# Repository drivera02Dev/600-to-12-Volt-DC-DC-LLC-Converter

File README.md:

# 600V-to-12V-DC-DC-Converter-Senior-Design-Project
## Team
- Caleb Rezmer 
- Drew Bixler 
- Hunter Kanne 
- Diego Rivera 
- Andrew Chandler 
- Wesley Mao

## Overview
This project was proposed by Caleb Rezmer for the FSAE club at Iowa State. This converter will go inside the electric formula car and it will use the 600 Volt battery from the car and step it down to 12 Volts at 30 Amps. It is stepped down to 12 Volts for the internals of the car such as lights, digital displays, fans, and anything else the team would want to add to the car that requires low voltage.

## Role
My role in the project was to make sure the power supply had the proper components it needs to function properly. I had to build and edit the schematic from the reference design we had. I had to verify that at the proper test points it was able to take that high voltage and keep the voltage at a steady 12 volts.

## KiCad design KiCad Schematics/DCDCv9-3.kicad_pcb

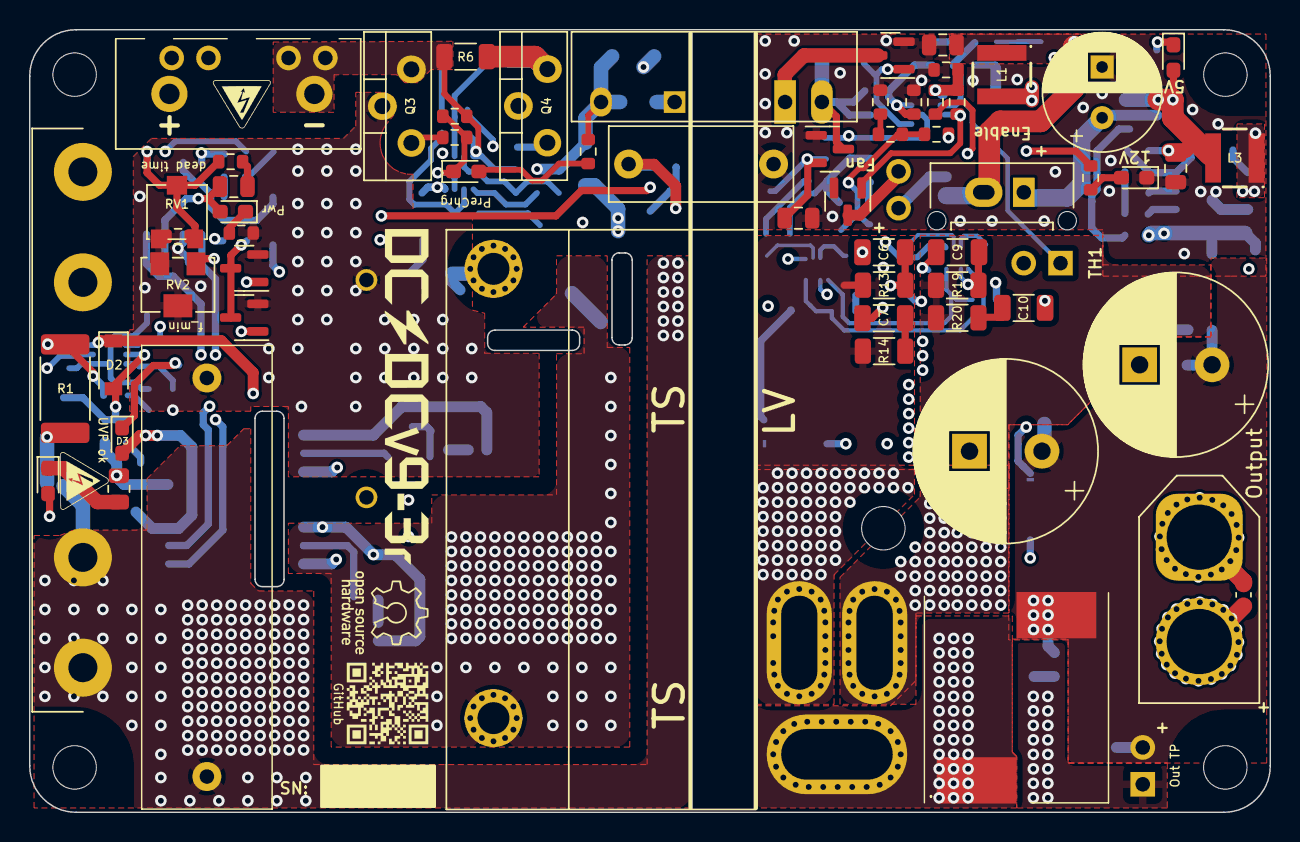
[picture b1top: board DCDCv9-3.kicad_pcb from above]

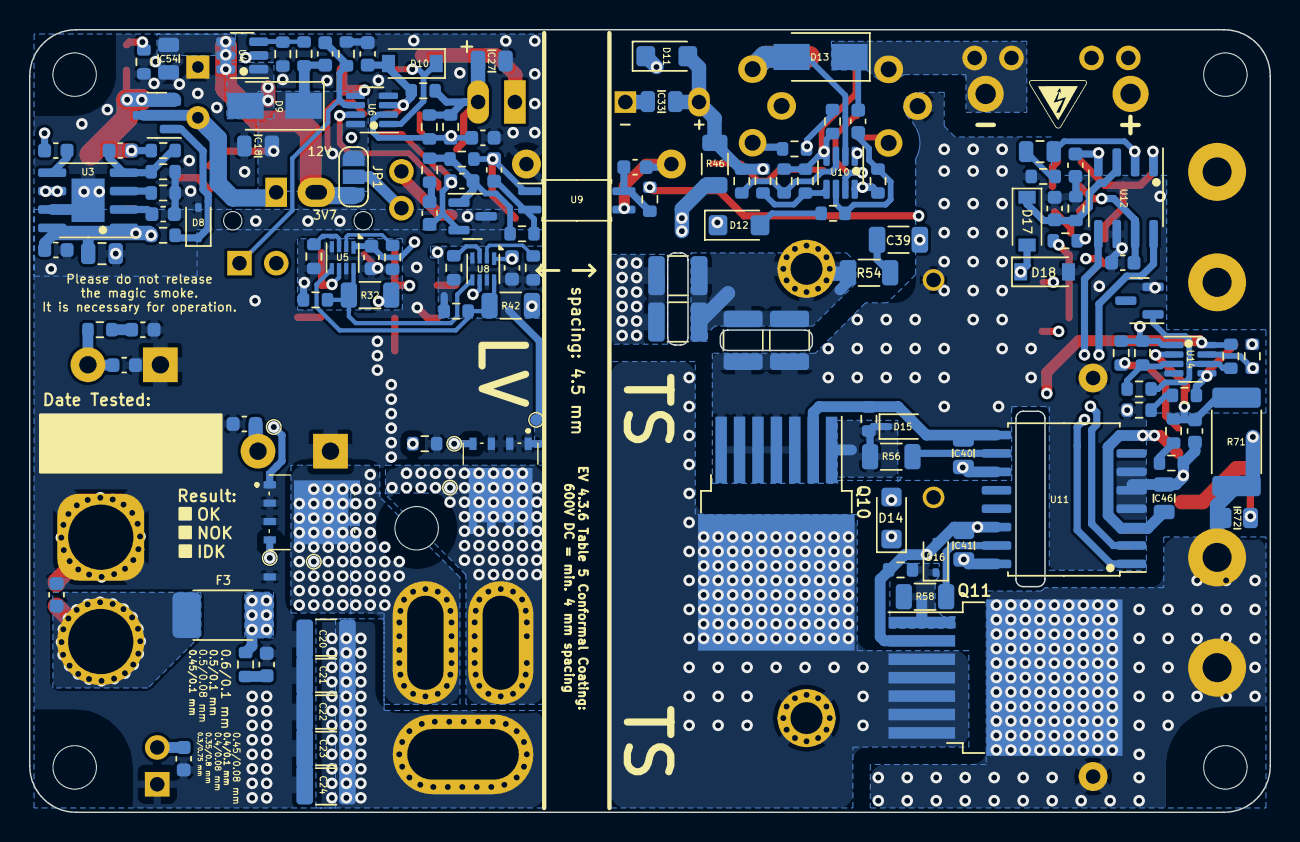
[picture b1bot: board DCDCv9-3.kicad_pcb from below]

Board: 4 copper layers, 85.6 x 54.0 mm, 206 parts (139 on the bottom side), 102 nets.

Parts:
C1: 2uF; MKP1848520704K2
C2, C15, C40, C41: 2.2uF; C_0805_2012Metric
C3: 22nF; R76UI22205050J
C4: 3.3nF; C_Disc_D12.5mm_W5.0mm_P10.00mm
C5, C33, C46: 10uF; C_0805_2012Metric
C6, C9: 1 nF; C_1206_3216Metric
C7, C10, C39: 470pF; C_1206_3216Metric
C8, C12, C18, C27, C42, C54: 22uF; C_0805_2012Metric
C11, C13: 2200uF; CP_Radial_D12.5mm_P5.00mm_symbol_inside
C14, C28: 100nF; C_0603_1608Metric
C16, C49, C50, C51, C52, C53, C55, C56, C57: 1nF; C_0603_1608Metric
C17, C19, C25, C31, C45: 1uF; C_0603_1608Metric
C20, C21, C22, C23, C24: 10uF; C_1210_3225Metric
C26, C44, C47: 22nF; C_0603_1608Metric
C29: 47pF; C_0603_1608Metric
C30, C32, C48: 10nF; C_0603_1608Metric
C34, C35, C36, C37: 5.6nF; C_1210_3225Metric
C38: 120pF; C_0603_1608Metric
C43: 470nF; C_0603_1608Metric
C_start1: 3.8V 25F Supercap; CP_Radial_D8.0mm_P3.50mm
D1: HV_Orange; LED_0603_1608Metric_Pad1.05x0.95mm_HandSolder
D2, D10, D17, D18: 1N4448; D_SOD-123
D3, D4, D5, D6, D7: Green; LED_0603_1608Metric_Pad1.05x0.95mm_HandSolder
D8, D15, D16: CDSOD323-T12; D_SOD-323
D9, D13: SS1H10; D_SMA
D11, D12, D14: VS-E7FX0212-M3/I; D_SMF
F1: 1.6A; Fuseholder0,25Zoll_32mm_littlefuse_102_122
F3: 20A; Bel_SMCF_Fuse_2410_6125Metric
HV_Logo_1, HV_Logo_1#2, HV_Logo_1#3: HV_Logo_1; HV_Logo_small
J1: Screw_Terminal_01x03; TerminalBlock_TE-282817-2_1x03_P5.00mm_90 Degrees updated v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
J2, J4, J6, J7, J8: Conn_01x02_Male; PinHeader_1x02_P2.54mm_Vertical
J3: Conn_01x02; Molex_Micro-Fit_3.0_43650-0215_1x02_P3.00mm_Vertical_combin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
J5: XT60 Male; AMASS_XT60-F_1x02_P7.20mm_Vertical
JP1: Fan Voltage Select; SolderJumper-3_P1.3mm_Open_RoundedPad1.0x1.5mm_NumberLabels
L1: 4.7uH; ASPI-4030S
L2: 1uH; 7443091100_v9.2
L3: 10uH; ASPI-4030S
NT1, NT2: NetTie_2; dummy_net_line_0.5mm
Q1, Q2, Q5, Q6, Q7: PMV20ENR; SOT-23
Q3: SIHP24N80AE-GE3; TO-220-3_Vertical_HV1.2mm
Q4: IXYP8N90C3; TO-220-3_Vertical_HV1.2mm
Q8, Q9: BSC027N06LS5ATMA1
Q10, Q11: IMBG65R050M2HXTMA1; TO-263-7_TabPin8
QR_Coode_1: QR_Coode; GitHub_QR_Code
R1, R71: 100M; R_2512_6332Metric_Pad1.40x3.35mm_HandSolder
R2, R72: 330k; R_0805_2012Metric
R3: 3.0k; R_0603_1608Metric
R4, R39, R41, R59, R61: 1k; R_0603_1608Metric
R5, R7, R9, R11, R15, R16, R21, R23, R30, R33, R40, R43, R51, R52, R55, R57, R63: 10k; R_0603_1608Metric
R6, R14, R20: 47; R_1206_3216Metric
R8, R10, R22, R29, R38, R48, R49: 2.2k; R_0603_1608Metric
R12: 910; R_0603_1608Metric
R13, R19: 100; R_1206_3216Metric
R17, R24: 27k; R_0603_1608Metric
R18, R27, R50: 470k; R_0603_1608Metric
R25: 240k; R_0603_1608Metric
R26, R45, R47, R53, R67, R70: 100k; R_0603_1608Metric
R28, R34, R66: 33k; R_0603_1608Metric
R31, R36: 4.7k; R_0603_1608Metric
R32, R42: 4.7; R_1206_3216Metric
R35: 330k; R_0603_1608Metric
R37: 47k; R_0603_1608Metric
R44: 510; R_0603_1608Metric
R46: 20; R_1206_3216Metric
R54: 10M; R_1206_3216Metric
R56, R58: 10; R_1206_3216Metric
R60: 82k; R_0603_1608Metric
R62, R69: 100M; R_0603_1608Metric
R64: 820k; R_0603_1608Metric
R65: 510k; R_0603_1608Metric
R68: 1.6M; R_0603_1608Metric
R73, R74: 10; R_0603_1608Metric
RV1: 20k; Potentiometer_Bourns_PVG3G
RV2: 10k; Potentiometer_Bourns_3214W_Vertical
T1: DIY Transformer ETD 39; Transformer_ETD39_uprightV3.6 (PSS 24V)
TH2: 1k PTC; R_0603_1608Metric
TP1, TP2, TP3, TP4, TP5, TP6: TestPoint; TestPoint_Pad_D0.8mm_DC-DC
TP8: GaN GND2; TestPoint_Pad_D0.8mm_DC-DC
U1: TBA 1-1212HI; Converter_DCDC_TRACO_TBA 1-1212HI-3kV-iso
U2: RT9058-90GVL; SOT-23
U3: MP4541_SOP8-EP; SOIC-8-1EP_3.9x4.9mm_P1.27mm_EP2.29x3mm XL7005
U4: TLV61048DBVR; SOT-23-6
U5, U8: NCP4305DMTTWG; WDFN-8_2x2mm_P0.5mm
U6, U10, U14: LM2904BIDDFR; SOT-23-8_DC-DC_v9
U7: TL431; SOT-23
U9: ACPL-217-50AE; SOIC-4_4.55x2.6mm_P1.27mm
U11: UCC21520DW; SOIC-16W_7.5x10.3mm_P1.27mm
U12: UCC25600; SOIC-8_3.9x4.9mm_P1.27mm
U13: ZXRE330ASA-7; SOT-23

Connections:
24V_TP: C11.1, C13.1, C50.2, C51.2, C52.2, F3.1, J4.1, L2.2, R17.1, R73.1, R74.1
+3V7: C8.1, C54.1, J3.2, JP1.3 (B), L1.1, U4.4 (~SHDN), U4.5 (IN), U4.6 (nc)
+9V: C5.1, C30.2, R39.1, U2.2 (VO), U9.1
+12V_HS: C41.2, D14.1 (K), U11.16 (VDDA)
+12V_IN: C2.2, C40.2, C45.2, C46.1, D2.1 (K), D3.2 (A), D4.2 (A), D11.1 (K), R70.1, U11.3 (VCCI), U11.8 (VCCI), U11.11 (VDDB), U12.7 (VCC), U14.8 (V+)
+12V_sw: C18.1, C19.2, C25.1, C27.1, C31.1, D9.1 (K), J8.1, JP1.1 (A), R16.1, R21.2, R27.1, R34.1, R35.2, R36.2, U1.1 (+VIN), U2.3 (VI), U5.1 (VCC), U6.8 (V+), U8.1 (VCC)
+24V: C15.2, C53.2, R26.2, U3.1 (EN), U3.8 (VIN)
+HV: C1.2, C34.1, C35.1, F1.2, Q11.8 (D), R1.1, R71.1, R72.1
+HV_in: F1.1, J1.2, J7.1, J7.2
-HV_in: C33.2, C38.1, D13.1 (K), J1.1, J6.1, J6.2, Q3.3 (S), R6.2, R7.2, R48.1, R50.1, R51.2, U1.5 (-VOUT), U10.4 (V-)
-HV_pc: C1.1, C3.2, C4.1, C32.2, C36.2, C37.2, C43.2, C44.1, C45.1, C46.2, C47.2, D12.1 (K), D18.2 (A), Q1.2 (S), Q2.2 (S), Q3.2 (D), Q4.2 (C), Q10.3 (S), Q10.4 (S), Q10.5 (S), Q10.6 (S), Q10.7 (S), R2.2, R3.2, R5.1, R59.2, R60.1, R65.2, R68.2, RV1.3, RV2.2, RV2.3, U9.3, U11.4 (GND), U11.5 (DIS), U11.6 (DT), U12.6 (GND), U13.2, U14.4 (V-)
/HB_out: Q10.8 (D), Q11.3 (S), Q11.4 (S), Q11.5 (S), Q11.6 (S), Q11.7 (S), T1.1 (AA)
/HS: U11.1 (INA), U12.8 (GD1)
/LS: U11.2 (INB), U12.5 (GD2)
/OC: C44.2, D17.1 (K), R60.2, U12.3 (OC)
/OTP_FAN: Q5.1 (G), R18.1, U6.7
/OTP_OFF: D10.1 (K), Q6.1 (G), U6.1
/OVP: Q2.1 (G), R69.1, U14.7
/Opc+: C32.1, R44.2, U9.4
/Synchronous Rectification/3: Q9.5 (D_1), Q9.6 (D_2), Q9.7 (D_3), Q9.8 (D_4), Q9.9 (D_5), R13.2, R14.1, T1.3 (SB), TP5.1
/Synchronous Rectification/5: Q8.5 (D_1), Q8.6 (D_2), Q8.7 (D_3), Q8.8 (D_4), Q8.9 (D_5), R19.2, R20.1, T1.5 (SA), TP3.1
/UVP: Q1.1 (G), R62.1, R63.1, U14.1
GND: C4.2, C5.2, C7.1, C8.2, C10.1, C11.2, C12.1, C13.2, C15.1, C17.1, C18.2, C20.2, C21.2, C22.2, C23.2, C24.2, C27.2, C28.1, C48.1, C49.1, C50.1, C51.1, C52.1, C53.1, C54.2, C55.1, C56.1, C57.1, C_start1.2 (-), D6.1 (K), D8.2 (A2), J4.2, J5.2, NT1.2, NT2.2, Q5.2 (S), Q6.2 (S), Q8.1 (S_1), Q8.2 (S_2), Q8.3 (S_3), Q9.1 (S_1), Q9.2 (S_2), Q9.3 (S_3), R10.2, R11.2, R15.1, R22.1, R23.2, R25.1, R28.2, R31.1, TH2.2, TP8.1, U2.1 (GND), U3.7 (GND), U4.2 (GND), U6.4 (V-), U7.3 (A)
unnamed: C2.1, R4.2
unnamed: C7.2, R14.2
unnamed: C10.2, R20.2
unnamed: C26.2, R37.1
unnamed: C30.1, R41.1, U9.2
unnamed: C39.2, R54.1
unnamed: C42.2, R59.1
unnamed: C56.2, R73.2
unnamed: C57.2, R74.2
unnamed: C_start1.1 (+), J3.1, Q7.3 (D)
unnamed: D1.2 (A), R72.2
unnamed: D1.1 (K), R2.1
unnamed: C47.1, D2.2 (A), R67.2, R71.2, U14.2 (-)
unnamed: D3.1 (K), R63.2
unnamed: D4.1 (K), R5.2
unnamed: D5.2 (A), R9.1
unnamed: D5.1 (K), R7.1, R8.2, U10.7
unnamed: D6.2 (A), R21.1
unnamed: C12.2, C16.2, D7.2 (A), L3.2, Q7.2 (S), R24.1
unnamed: D7.1 (K), R22.2
unnamed: D8.1 (A1), Q7.1 (G), R26.1
unnamed: D9.2 (A), L1.2, U4.1 (SW)
unnamed: C48.2, D10.2 (A), R11.1, R34.2, U6.3 (+)
unnamed: C33.1, D11.2 (A), R9.2, R45.2, R46.2, R47.2, R53.2, U1.7 (+VOUT), U10.8 (V+)
unnamed: D12.2 (A), R52.1
unnamed: D13.2 (A), Q4.3 (E), R6.1, U10.2 (-)
unnamed: D14.2 (A), R46.1
unnamed: D15.1 (A1), Q10.1 (G), R55.1, R56.1
unnamed: C40.1, D15.2 (A2), Q10.2 (DS), R55.2, U11.9 (VSSB)
unnamed: D16.1 (A1), Q11.1 (G), R57.1, R58.1
unnamed: C41.1, D16.2 (A2), Q11.2 (DS), R57.2, U11.14 (VSSA)
unnamed: C39.1, D17.2 (A), D18.1 (K)
unnamed: J2.1, JP1.2 (C)
unnamed: J2.2, Q5.3 (D)
unnamed: C49.2, C55.2, F3.2, J5.1
unnamed: C19.1, J8.2, R31.2, U6.6 (-)
unnamed: Q1.3 (D), Q2.3 (D), R61.1
unnamed: Q3.1 (G), R8.1
unnamed: Q4.1 (G), R49.1
unnamed: Q8.4 (G), R32.1, TP2.1
unnamed: Q9.4 (G), R42.1, TP4.1
unnamed: R10.1, R12.2
unnamed: R49.2, R51.1, U10.1
unnamed: R65.1, R66.2
unnamed: R67.1, R68.1
unnamed: C34.2, C35.2, C36.1, C37.1, R54.2, T1.2 (AB)
unnamed: C20.1, C21.1, C22.1, C23.1, C24.1, L2.1, T1.4 (SC)
unnamed: C14.2, U3.5 (BST)
unnamed: C16.1, R23.1, R24.2, U3.4 (FB)
unnamed: R25.2, U3.3 (FREQU)
unnamed: C14.1, L3.1, U3.6 (SW)
unnamed: C17.2, U3.2 (VCC)
unnamed: R27.2, R28.1, U4.3 (FB)
unnamed: C9.2, R19.1, U5.6 (CS)
unnamed: R30.2, R32.2, U5.8 (DRV), U8.5 (TRIG/DIS)
unnamed: C9.1, C25.2, NT1.1, R29.1, R30.1, R33.1, TP1.1, U5.4 (LLD), U5.7 (GND)
unnamed: R33.2, U5.2 (MIN_TOFF)
unnamed: R29.2, U5.3 (MIN_TON)
unnamed: R40.2, R42.2, U5.5 (TRIG/DIS), U8.8 (DRV)
unnamed: C28.2, R35.1, R36.1, TH2.1, U6.2 (-)
unnamed: R15.2, R16.2, R18.2, U6.5 (+)
unnamed: C29.2, R37.2, R39.2, R41.2, U7.1 (K)
unnamed: C26.1, C29.1, R12.1, R17.2, U7.2 (REF)
unnamed: C6.2, R13.1, U8.6 (CS)
unnamed: C6.1, C31.2, NT2.1, R38.1, R40.1, R43.1, TP6.1, U8.4 (LLD), U8.7 (GND)
unnamed: R43.2, U8.2 (MIN_TOFF)
unnamed: R38.2, U8.3 (MIN_TON)
unnamed: R45.1, R48.2, U10.3 (+)
unnamed: R47.1, R50.2, U10.5 (+)
unnamed: C38.2, R52.2, R53.1, U10.6 (-)
unnamed: R58.2, U11.15 (OUTA)
unnamed: R56.2, U11.10 (OUTB)
unnamed: R3.1, R4.1, RV1.1, RV1.2, U12.1 (DT)
unnamed: C42.1, R44.1, RV2.1, U12.2 (RT)
unnamed: C43.1, R61.2, U12.4 (SS)
unnamed: R62.2, R64.1, U14.3 (+)
unnamed: R1.2, R66.1, R69.2, U14.5 (+)
unnamed: R64.2, R70.2, U13.1, U14.6 (-)
OTP_FET: Q6.3 (D), U1.2 (-VIN)

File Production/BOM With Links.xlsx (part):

Reference | Value | Manufacturer_Part_Number |  |  | DigiKey Link |  |  |  |  |  |  |  |  |  |  |  |  |  | Price | # of Parts | Total (Parts Only)
C1 | 2uF | MKP1848520704K2 |  | Mouser | https://www.mouser.com/ProductDetail/Vishay-Roederstein/MKP1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 |  |  |  |  |  |  |  |  |  |  |  |  |  | 3.92 | 1 | 141.76999999999992
C3 | 22nF | R76UI22205050J |  |  | https://www.digikey.com/en/products/detail/kemet/R76UI222050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 |  |  |  |  |  |  |  |  |  |  |  |  |  | 0.88 | 1
C4 | 3.3nF | VY1332M59Y5UQ63V0 |  |  | https://www.digikey.com/en/products/detail/vishay-beyschlag-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 |  |  |  |  |  |  |  |  |  |  |  |  |  | 0.74 | 1
C29 | 1V | C0603C470J1HACTU |  |  | https://www.digikey.com/en/products/detail/kemet/C0603C470J1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 |  |  |  |  |  |  |  |  |  |  |  |  |  | 0.1 | 1
C39 | 470pF | 885342208005 |  |  | https://www.digikey.com/en/products/detail/w%C3%BCrth-elektr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 |  |  |  |  |  |  |  |  |  |  |  |  |  | 0.21 | 1
C43 | 470nF | UMK107ABJ474KA-T |  |  | https://www.digikey.com/en/products/detail/taiyo-yuden/UMK10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 |  |  |  |  |  |  |  |  |  |  |  |  |  | 0.13 | 1
C11,C13 | 2200uF | UHW1V222MHD |  |  | https://www.digikey.com/en/products/detail/nichicon/UHW1V222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 |  |  |  |  |  |  |  |  |  |  |  |  |  | 2.4300000000000002 | 1
C14,C28 | 100nF | HMJ107BB7104KAHT |  |  | https://www.digikey.com/en/products/detail/taiyo-yuden/HMJ10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 |  |  |  |  |  |  |  |  |  |  |  |  |  | 0.54 | 2
C15,C40,C41 | 2.2uF | CL21B225KBYNNWE |  | Mouser | https://www.mouser.com/ProductDetail/Samsung-Electro-Mechani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 |  |  |  |  |  |  |  |  |  |  |  |  |  | 0.23 | 1
C16,C49,C50,C51,C52,C53,C56,C57 | 1nF | 885342206003 |  |  | https://www.digikey.com/en/products/detail/w%C3%BCrth-elektr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 |  |  |  |  |  |  |  |  |  |  |  |  |  | 0.8 | 8
C17,C19,C25,C31,C45 | 1uF | CL10B105KB9VPJC |  | Substitute | https://www.digikey.com/en/products/detail/samsung-electro-m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 |  |  |  |  |  |  |  |  |  |  |  |  |  | 1.44 | 4
C20,C21,C22,C23,C24 | 47uF | MSAST32MAB5476MPNDT1 | Mouser | Swapped | https://www.mouser.com/ProductDetail/TAIYO-YUDEN/MSAST32MAB5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 |  |  |  |  |  |  |  |  |  |  |  |  |  | 3.92 | 4
C26,C44,C47 | 22nF | C0603C223K1RAC |  |  | https://www.digikey.com/en/products/detail/kemet/C0603C223K1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 |  |  |  |  |  |  |  |  |  |  |  |  |  | 0.30000000000000004 | 3
C30,C32,C48 | 10nF | C0603C103K2RECTU |  |  | https://www.digikey.com/en/products/detail/kemet/C0603C103K2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 |  |  |  |  |  |  |  |  |  |  |  |  |  | 0.44999999999999996 | 3
C34,C35,C36,C37 | 5.6nF | C1210C562JDGACAUTO |  |  | https://www.digikey.com/en/products/detail/kemet/C1210C562JD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 |  |  |  |  |  |  |  |  |  |  |  |  |  | 7.72 | 4
C5,C33,C46 | 10uF | TMK212BBJ106KG-T |  |  | https://www.digikey.com/en/products/detail/taiyo-yuden/TMK21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 |  |  |  |  |  |  |  |  |  |  |  |  |  | 0.48 | 3
C6,C9 | 1 nF | SH31B102K631CT |  | Mouser | https://www.mouser.com/ProductDetail/Walsin/SH31B102K631CT?q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 |  |  |  |  |  |  |  |  |  |  |  |  |  | 0.22 | 2
C8,C12,C18,C27,C42,C54 | 22uF | CL21A226MAYNNNE |  |  | https://www.digikey.com/en/products/detail/samsung-electro-m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 |  |  |  |  |  |  |  |  |  |  |  |  |  | 1.44 | 6
C_start1 | 3.8V 25F Supercap | VMF256M3R8 |  |  | https://www.digikey.com/en/products/detail/cornell-dubilier-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 |  |  |  |  |  |  |  |  |  |  |  |  |  | 5.33 | 1
D1 | HV_Orange | APTD1608LSECK/J4-PF |  |  | https://www.digikey.com/en/products/detail/kingbright/APTD16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 |  |  |  |  |  |  |  |  |  |  |  |  |  | 0.59 | 1
D11,D12,D14 | VS-E7FX0212-M3/I | VS-E7FX0212-M3/I |  |  | https://www.digikey.com/en/products/detail/vishay-general-se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 |  |  |  |  |  |  |  |  |  |  |  |  |  | 1.32 | 3
D2,D10,D17,D18 | 1N4448 | 1N4448WQ-7-F |  |  | https://www.digikey.com/en/products/detail/diodes-incorporat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 |  |  |  |  |  |  |  |  |  |  |  |  |  | 0.4 | 4
D3,D4,D5,D6,D7 | Green | IN-S63AT5G |  | Mouser | https://www.mouser.com/ProductDetail/Inolux/IN-S63AT5G?qs=fA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 |  |  |  |  |  |  |  |  |  |  |  |  |  | 1.25 | 5
D8,D15,D16 | CDSOD323-T12 | CDSOD323-T12 |  |  | https://www.digikey.com/en/products/detail/bourns-inc/CDSOD3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 |  |  |  |  |  |  |  |  |  |  |  |  |  | 1.83 | 3
D9,D13 | SS1H10 | SS1H10-M3/61T |  |  | https://www.digikey.com/en/products/detail/vishay-general-se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 |  |  |  |  |  |  |  |  |  |  |  |  |  | 0.64 | 2
F1 | 1.6A | 0ADBC1600-BE |  |  | https://www.digikey.com/en/products/detail/bel-fuse-inc/0ADB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 |  |  |  |  |  |  |  |  |  |  |  |  |  | 5.87 | 1
F2 | 500mA | 0154.500DR |  |  | https://www.digikey.com/en/products/detail/littelfuse-inc/01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 |  |  |  |  |  |  |  |  |  |  |  |  |  | 3.87 | 1
F3 | 30A | CB61F30A-TR1 |  | Swapped | https://www.digikey.com/en/products/detail/eaton-electronics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 |  |  |  |  |  |  |  |  |  |  |  |  |  | 0.56000000000000005 | 1
F1.1,F1.2 | ~ | 01220083Z |  |  | https://www.digikey.com/en/products/detail/littelfuse-inc/01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 |  |  |  |  |  |  |  |  |  |  |  |  |  | 1.72 | 2
J1 | Screw_Terminal_01x03 | 282828-2 |  |  | https://www.digikey.com/en/products/detail/te-connectivity-a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 |  |  |  |  |  |  |  |  |  |  |  |  |  | 2.37 | 1
J1.1 | Screw_Terminal_01x03 | 284051-2 |  | Mouser | https://www.mouser.com/ProductDetail/TE-Connectivity/284051-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 |  |  |  |  |  |  |  |  |  |  |  |  |  | 1.45 | 1
J1.2 | Screw_Terminal_01x03 | 282809-2 |  |  | https://www.digikey.com/en/products/detail/te-connectivity-a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 |  |  |  |  |  |  |  |  |  |  |  |  |  | 2.69 | 1
J3 | Conn_01x02 | 43650-0215 |  |  | https://www.digikey.com/en/products/detail/molex/0436500215/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 |  |  |  |  |  |  |  |  |  |  |  |  |  | 0.89 | 1
J3 | Conn_01x02 | 43645-0200 |  |  | https://www.digikey.com/en/products/detail/molex/0436450200/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 |  |  |  |  |  |  |  |  |  |  |  |  |  | 0.31 | 1
J5 | XT60 Male | ~
J5.1 | XT60 Female (wrong symbol ik) | ~
J2,J4,J6,J7,J8 | Conn_01x02_Male | 42375-2486 |  | Mouser | https://www.mouser.com/ProductDetail/Molex/42375-2486?qs=ZGc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 |  |  |  |  |  |  |  |  |  |  |  |  |  | 0.5 | 5
J3.2,J3.3 | Conn_01x01_Pin | 35044-9102 |  | Mouser | https://www.mouser.com/ProductDetail/Molex/35044-9102?qs=ZlM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 |  |  |  |  |  |  |  |  |  |  |  |  |  | 0.2 | 2
JP1 | Fan Voltage Select | ~
L1 | 4.7uH | ASPI-4030S-4R7M-T |  |  | https://www.digikey.com/en/products/detail/abracon-llc/ASPI-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 |  |  |  |  |  |  |  |  |  |  |  |  |  | 0.26 | 1
L2 | 800 nH | 7443091080 | Mouser | Swapped | https://www.mouser.com/ProductDetail/Wurth-Elektronik/744309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 |  |  |  |  |  |  |  |  |  |  |  |  |  | 3.01 | 1
L3 | 10uH | ASPI-4030S-100M-T |  |  | https://www.digikey.com/en/products/detail/abracon-llc/ASPI-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 |  |  |  |  |  |  |  |  |  |  |  |  |  | 0.26 | 1
M1 | Fan | ~
Q3 | SIHP24N80AE-GE3 | SIHP24N80AE-GE3 |  | MOSFET | https://www.digikey.com/en/products/detail/vishay-siliconix/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
Q4 | IXYP8N90C3 | IXYP8N90C3 | Mouser | MOSFET | IXYP8N90C3 IXYS | Mouser
Q1,Q2,Q5,Q6,Q7 | PMV20ENR | PMV20ENR |  |  | https://www.digikey.com/en/products/detail/nexperia-usa-inc/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 |  |  |  |  |  |  |  |  |  |  |  |  |  | 2.4 | 5
Q10,Q11 | IMBG65R050M2HXTMA1 | IMBG65R050M2HXTMA1 |  |  | https://www.digikey.com/en/products/detail/infineon-technolo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 |  |  |  |  |  |  |  |  |  |  |  |  |  | 15.64 | 2
Q8,Q9 | BSC027N06LS5ATMA1 | BSC027N06LS5ATMA1 |  |  | https://www.digikey.com/en/products/detail/infineon-technolo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 |  |  |  |  |  |  |  |  |  |  |  |  |  | 5.46 | 2
R6 | 47 | ERJ-P08J470V |  |  | https://www.digikey.com/en/products/detail/panasonic-electro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 |  |  |  |  |  |  |  |  |  |  |  |  |  | 0.15 | 1
R25 | 240k | AC0603FR-07240KL |  |  | https://www.digikey.com/en/products/detail/yageo/AC0603FR-07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 |  |  |  |  |  |  |  |  |  |  |  |  |  | 0.1 | 1
R35 | 330k | AC0603JR-07330KL |  |  | https://www.digikey.com/en/products/detail/yageo/AC0603JR-07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 |  |  |  |  |  |  |  |  |  |  |  |  |  | 0.1 | 1
R37 | 47k | RC0603FR-0747KL |  |  | https://www.digikey.com/en/products/detail/yageo/RC0603FR-07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 |  |  |  |  |  |  |  |  |  |  |  |  |  | 0.1 | 1
R44 | 510 | CRCW0603510RFKEBC |  | Substitute | https://www.digikey.com/en/products/detail/vishay-dale/CRCW0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 |  |  |  |  |  |  |  |  |  |  |  |  |  | 0.1 | 1
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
